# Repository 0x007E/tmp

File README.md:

# `TMP` - Temperature Warning (Temperaturwarnung)

The `TMP` is a board with an [LM358](#additional-information) or any other 2-channel operational amplifier. The board itself is driven with a voltage of `5V`. It converts the temperature (0° - 100°) from an [KTY81/210](#additional-information) to a voltage. This voltage can be coupled onboard with a Schmitt-Trigger to change the status of the connected LEDs (`green`, `red`).

Optional the converted temperature can be digitalized through an A/D converter and sent to a terminal through UART. A demo how this can be done is attached and can be tested with an [ATmega16A](#additional-information).

| Experience | Level |
|:------------|:-----:|
| Soldering   |  |
| Software    |  |

# Downloads

| Type      | File               | Description              |
|:---------:|:------------------:|:-------------------------|
| Simulation | [asc](https://github.com/0x007E/tmp/raw/refs/heads/main/TMP.asc) | LTSpice Simulation | 
| Lochmaster | [lm4](https://github.com/0x007E/tmp/raw/refs/heads/main/TMP.LM4) | Stripe grid circuit board | 
| Schematic | [pdf](https://github.com/0x007E/tmp/releases/latest/download/schematic.pdf) / [cadlab](https://cadlab.io/project/28588/main/files) | Schematic files |
| Board | [pdf](https://github.com/0x007E/tmp/releases/latest/download/pcb.pdf) / [cadlab](https://cadlab.io/project/28588/main/files) | Board file |
| Drill | [pdf](https://github.com/0x007E/tmp/releases/latest/download/drill.pdf) | Drill file |
| BoM | [xlsx](https://github.com/0x007E/tmp/releases/latest/download/bom.xlsx) / [html](https://github.com/0x007E/tmp/releases/latest/download/ibom.html)          | Bill of Material as Excel/interactive HTML |
| PCB    | [zip](https://github.com/0x007E/tmp/releases/latest/download/kicad.zip) / [tar](https://github.com/0x007E/tmp/releases/latest/download/kicad.tar.gz)    | KiCAD/Gerber/BoM/Drill files       |
| Firmware | [zip](https://github.com/0x007E/tmp/releases/latest/download/firmware.zip) / [tar](https://github.com/0x007E/tmp/releases/latest/download/firmware.tar.gz) | Demo Firmware for ATmega16 |

# Hardware

The pcb is created with `KiCAD`. All files are built with `github actions` so that they are ready for a production environment.

## PCB

The circuit board is populated on one side. The best way for soldering the `SMD` components is within a vapor phase soldering system and for the `THT` components with a standard system.

### Top Layer

### Bottom Layer

# Configuration

To configure the `TMP` some reference voltages needs to be modified. The reference of `TP2` has to be around `~1V` and is adjusted through `RV1`. On `J2` the [KTY81/210](#additional-information) should be connected. To setup the amplification a mutimeter with temperature measurement function is needed. The voltage on `TP3` can be calculated through the following equation:

$U_{TP3}=\frac{2.5}{100}*𝜗+1$

Calculate $U_{TP3}$ with the current temperature and setup the voltage on `TP3` to the calculated value with `RV2`. The Equation is Designed for the following parameters:

| $U_{TP3}/[V]$ | Temperature $𝜗/[°C]$ |
|:--------:|:-------------------------:|
| 1        | 0                         |
| 3.5      | 100                       |

On Jumper `J3/1` the generated voltage from the captured temperature can be measured. To connect the temperature measurement to the warning system jumper `J3` has to be shorten.

With `RV3` the limit to generate a state change of the leds can be set to a value between `2°` to `98°`. With `RV4` the hysteresis of the Schmitt-Trigger can be adjusted.

# Software

The demo firmware (`ATmega16A`) of the `TMP` can be used to digitalize the voltage with an A/D converter and transmit the data over uart to a terminal.

## Dataflow diagram

## Structogram

# Additional Information

| Type       | Link               | Description              |
|:----------:|:------------------:|:-------------------------|
| LM358 | [pdf](https://www.ti.com/lit/ds/symlink/lm358.pdf) | Dual operational amplifier |
| KTY81 | [pdf](https://www.nxp.com/docs/en/data-sheet/KTY81_SER.pdf) | Temperature sensor 2 k0hm |
| ATmega16A | [pdf](https://ww1.microchip.com/downloads/en/devicedoc/atmel-8154-8-bit-avr-atmega16a_datasheet.pdf) | Microchip ATmega16A Datasheet |

---

R. GAECHTER

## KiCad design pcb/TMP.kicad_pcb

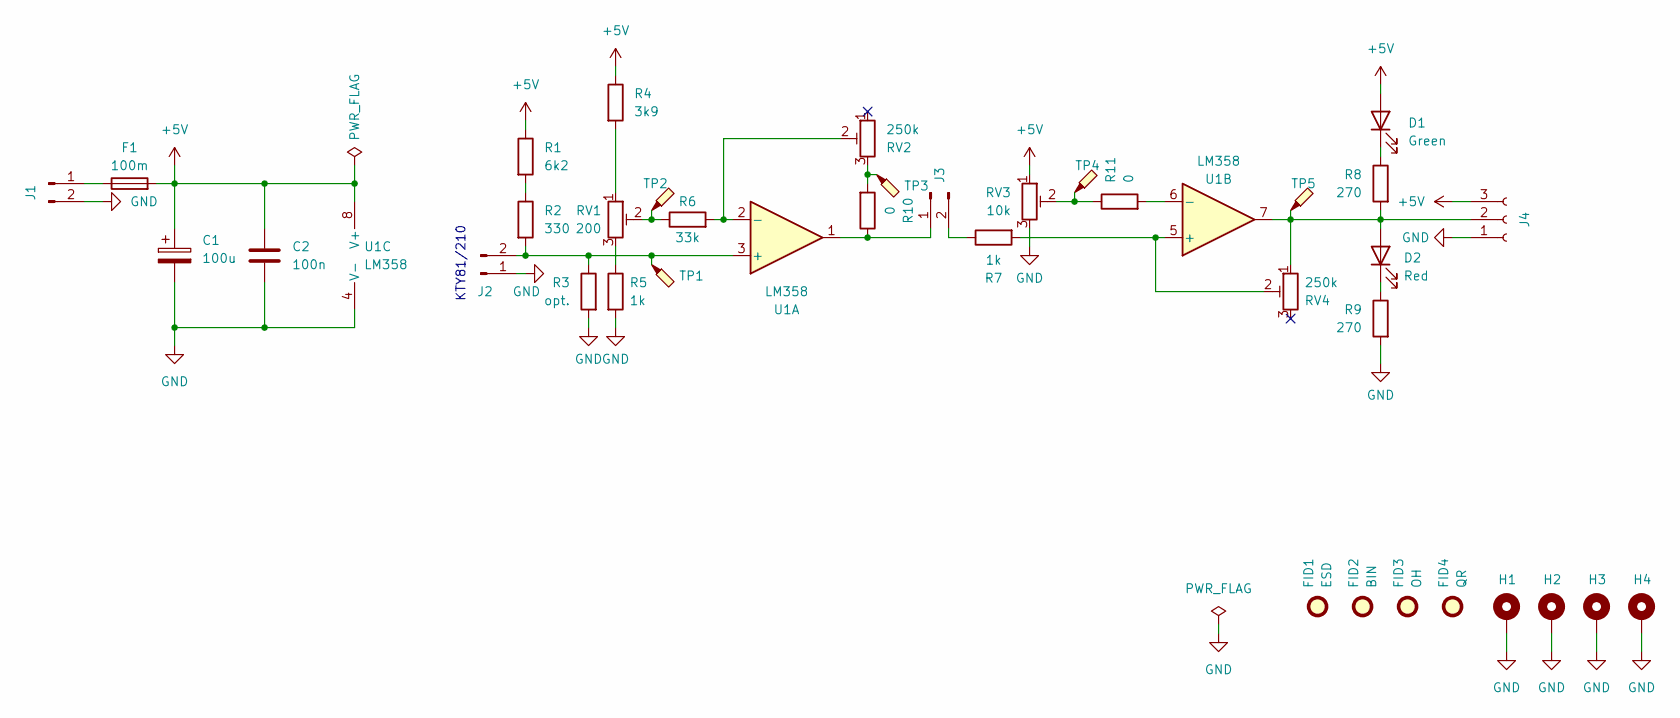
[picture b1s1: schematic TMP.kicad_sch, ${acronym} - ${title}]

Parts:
C1: 100u; CP_Elec_8x6.5
C2: 100n; C_1206_3216Metric
D1: Green; LED_1206_3216Metric
D2: Red; LED_1206_3216Metric
F1: 100m; Fuse_1206_3216Metric
FID1: ESD; ESD-Logo_6.6x6mm_SilkScreen
FID2: BIN; WEEE-Logo_4.2x6mm_SilkScreen
FID3: OH; OSHW-Logo_5.7x6mm_SilkScreen
FID4: QR; QR_0x007e
H1, H2, H3, H4: MountingHole_Pad; MountingHole_3.2mm_M3_DIN965_Pad
J1, J3: Conn_01x02_Pin; PinHeader_1x02_P2.54mm_Vertical
J2: Conn_01x02_Pin; WAGO_2060-402_998-404
J4: Conn_01x03_Socket; PinHeader_1x03_P2.54mm_Vertical
R1: 6k2; R_1206_3216Metric
R2: 330; R_1206_3216Metric
R3: opt.; R_1206_3216Metric
R4: 3k9; R_1206_3216Metric
R5, R7: 1k; R_1206_3216Metric
R6: 33k; R_1206_3216Metric
R8, R9: 270; R_1206_3216Metric
R10: 0; R_Axial_DIN0309_L9.0mm_D3.2mm_P12.70mm_Horizontal
R11: 0; R_1206_3216Metric
RV1: 200; Potentiometer_Bourns_3296W_Vertical
RV2, RV4: 250k; Potentiometer_Bourns_3296W_Vertical
RV3: 10k; Potentiometer_Bourns_3296W_Vertical
TP1, TP2, TP3, TP4, TP5: TestPoint_Probe; TestPoint_Pad_D1.5mm
U1: LM358; SOIC-8_3.9x4.9mm_P1.27mm

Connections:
+5V: C1.1, C2.1, D1.2 (A), F1.2, J4.3, R1.1, R4.1, RV3.1, U1.8 (V+)
GND: C1.2, C2.2, H1.1, H2.1, H3.1, H4.1, J1.2, J2.1, J4.1, R3.2, R5.2, R9.2, RV3.3, U1.4 (V-)
unnamed: D1.1 (K), R8.1
unnamed: D2.2 (A), J4.2, R8.2, RV4.1, TP5.1, U1.7
unnamed: D2.1 (K), R9.1
unnamed: F1.1, J1.1
unnamed: J2.2, R2.2, R3.1, TP1.1, U1.3 (+)
unnamed: J3.1, R10.1, U1.1
unnamed: J3.2, R7.1
unnamed: R1.2, R2.1
unnamed: R4.2, RV1.1
unnamed: R5.1, RV1.3
unnamed: R6.1, RV1.2, TP2.1
unnamed: R10.2, RV2.3, TP3.1
unnamed: R11.1, RV3.2, TP4.1
unnamed: R6.2, RV2.2, U1.2 (-)
unnamed: R7.2, RV4.2, U1.5 (+)
unnamed: R11.2, U1.6 (-)

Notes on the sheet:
KTY81/210

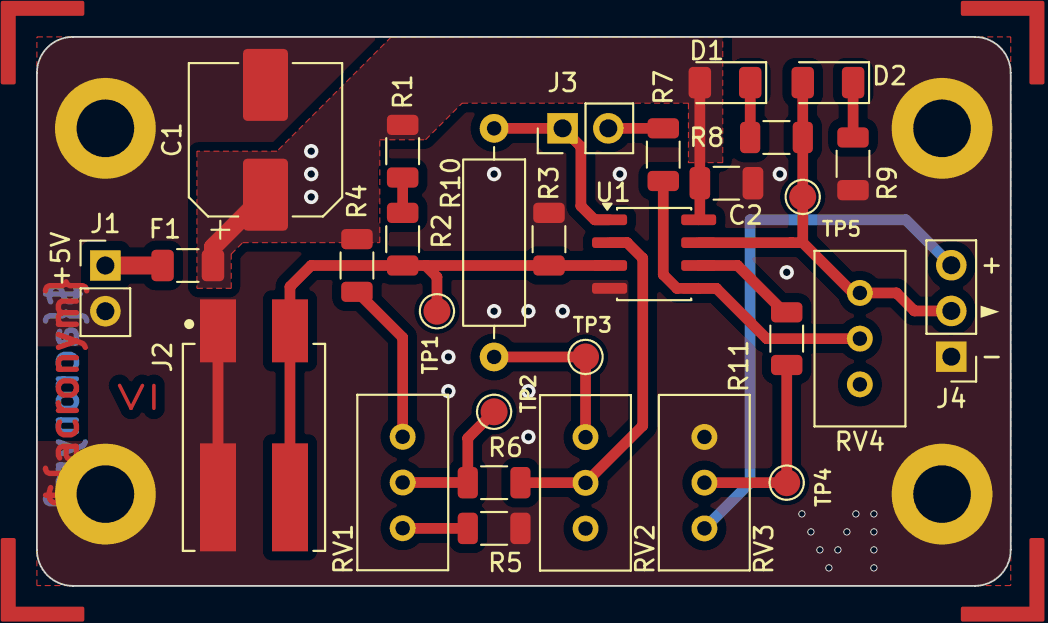
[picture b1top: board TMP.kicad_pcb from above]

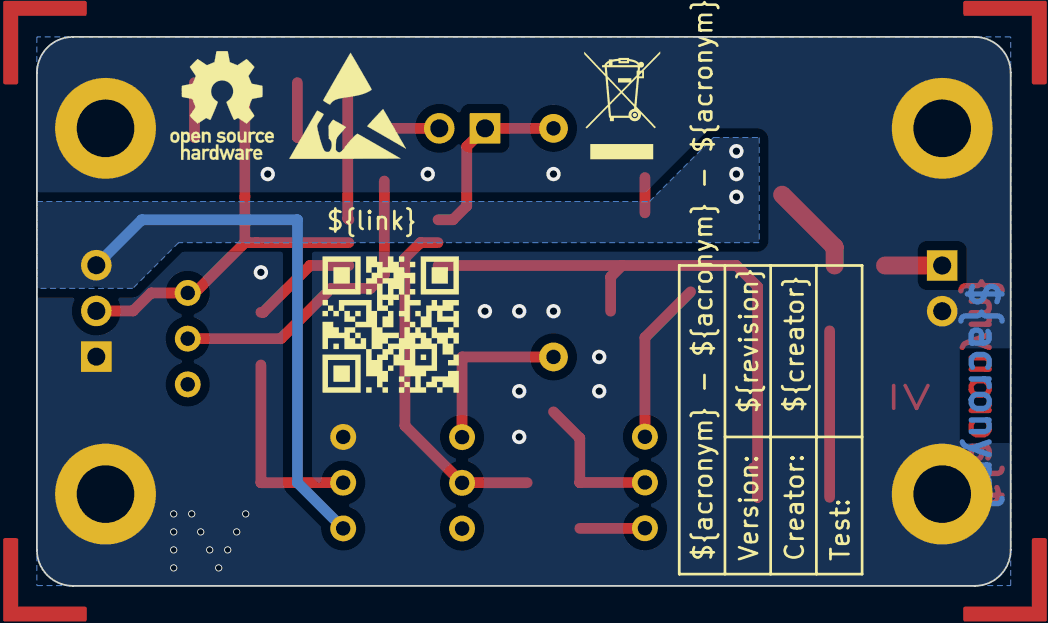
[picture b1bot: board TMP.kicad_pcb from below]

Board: 2 copper layers, 54.1 x 30.5 mm, 38 parts (4 on the bottom side), 18 nets.

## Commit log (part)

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2024-10-23 Add README
2024-10-23 Create pipeline
2024-10-23 Fix pipeline
2024-10-23 Fix firmware
2024-10-23 Change config
2024-10-23 Fix wrong version
2026-03-18 Fix vendor/vendorid at bom
2026-03-18 Optimize download section
2026-03-18 Rearrange silkscreen references

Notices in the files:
README.md:
License CC By-NC-SA
parts and their libraries:
license: CC BY-NC-SA 4.0
